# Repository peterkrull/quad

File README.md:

> [!TIP]
> The Rust-based flight control firmware is maintained in its own repository - [**Holsatus Flight**](https://github.com/holsatus/holsatus-flight)

---

# Project quad

This git repository is a personal project of mine to develop an open-source autonomous quad copter using cheap off-the-shelf components in conjunction with control theory and state estimation. As much as possible, any auxiliary tools and documentation I produce, will also be a part of the repository.

## Getting Rusty

The [firmware](/software/rusty-quad) is written in the Rust programming language. This is in contrast to most flight controllers (and embedded devices in general) which use C or C++. The reason for choosing Rust is quite simple: it is a modern language. It can guarantee many things about the validity of memory at compile time, allows for writing high-level code, that runs at low-level speeds, and feels good to write; once you become friendly with the borrow checker.

### [*YouTube* : Demo of wireless data plotting and responsive controls](https://www.youtube.com/watch?v=jQ53PiUz8Us)

---

## Directory contents

- **[3dparts](/3dparts/)** - 3D models used in the project as STEP and .obj files.
- **[docs](/docs/)** - Documentation and learning material used in the project.
- **[hardware](/hardware/)** - Schematics, and PCB layouts as well as finished gerber files.
- **[images](/images/)** - Photos used in readme and some documentation.
- **[software](/software/)** - Software related to the project, including simulations, firmware, etc.
- **[tests](/tests/)** - Results from test conducted during this project

---

## Related repositories

During this project, some additional tools were developed, that reside in their own repositories.

### Rust crates

- [Async no-std ICM-20948 driver](https://github.com/peterkrull/icm20948-async)
- [Dshot driver for RP2040 PIO](https://github.com/peterkrull/dshot-pio)
- [Magnetometer calibration algorithm](https://github.com/peterkrull/mag-calibrator-rs)
- [Linear multi-sensor Kalman filter](https://github.com/peterkrull/kalman_filter_rust/)
- [(Forked) no-std SBUS-parser](https://github.com/peterkrull/sbus)

---

## License

This work is licensed under GPLv3.

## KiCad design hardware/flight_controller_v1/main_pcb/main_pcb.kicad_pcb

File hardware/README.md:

# Hardware

While a perfboard-based flight controller is fully capable, it is also heavy, large and labor intensive to manufacture. A compact and integrated PCB is a natural next step to reduce complexity, increase flexibility and reproducability.

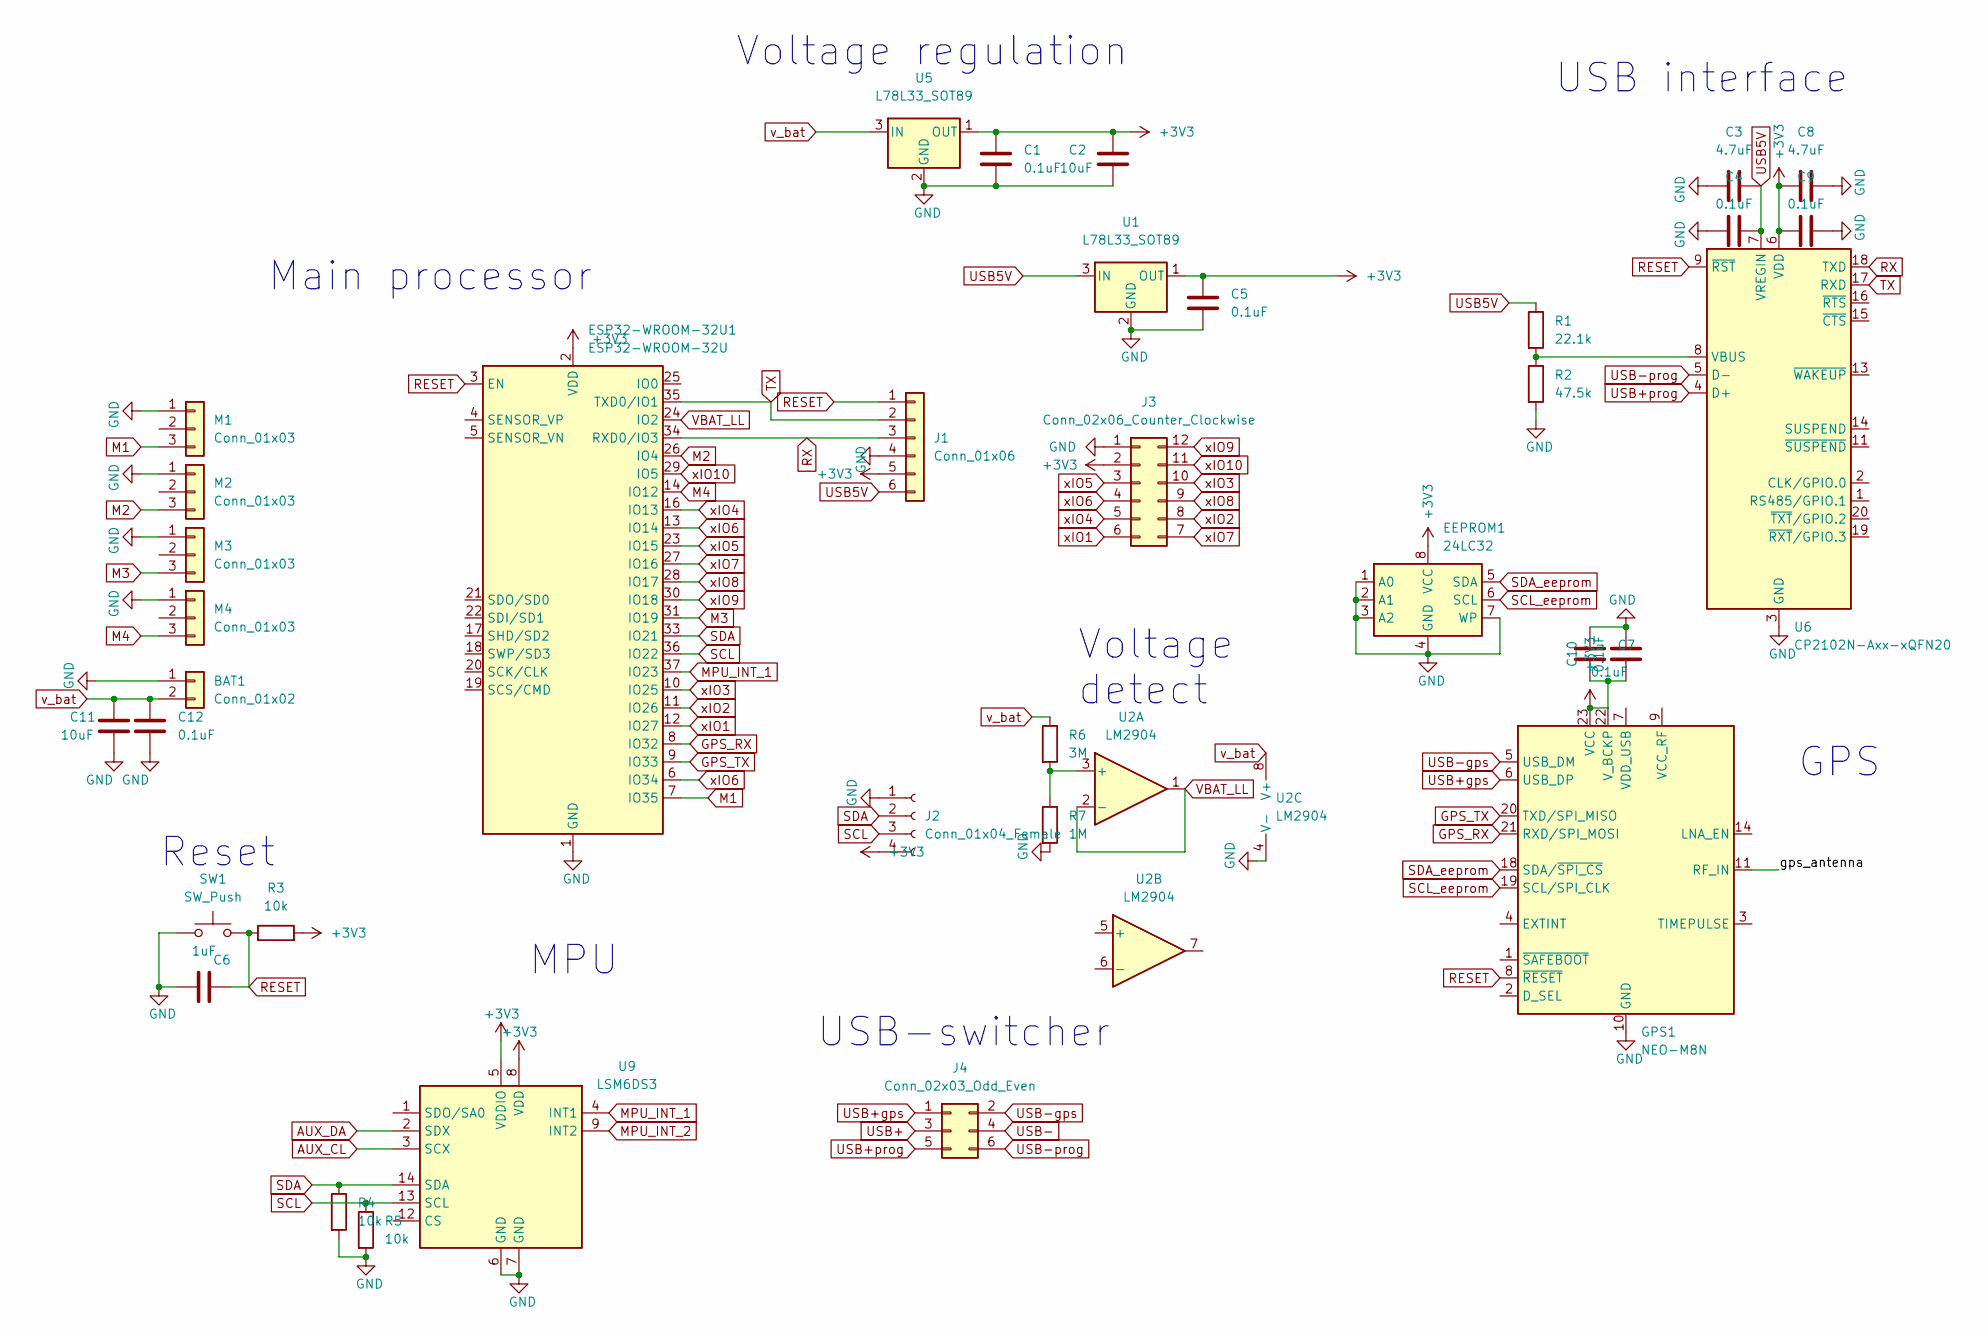
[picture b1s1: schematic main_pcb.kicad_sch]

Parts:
BAT1: Conn_01x02; PinHeader_1x02_P2.54mm_Vertical
C1, C4, C5, C7, C9, C10, C12: 0.1uF; C_0805_2012Metric
C2: 10uF; CP_Elec_5x4.5
C3, C8: 4.7uF; C_0805_2012Metric
C6: 1uF; C_0805_2012Metric
C11: 10uF; C_0805_2012Metric
EEPROM1: 24LC32; TSSOP-8_4.4x3mm_P0.65mm
ESP32-WROOM-32U1: ESP32-WROOM-32U
GPS1: NEO-M8N; ublox_NEO
J1: Conn_01x06; PinHeader_1x06_P2.54mm_Vertical
J2: Conn_01x04_Female; PinHeader_1x04_P2.54mm_Vertical
J3: Conn_02x06_Counter_Clockwise; PinHeader_2x06_P2.54mm_Vertical
J4: Conn_02x03_Odd_Even; PinHeader_2x03_P2.54mm_Vertical
M1, M2, M3, M4: Conn_01x03; PinHeader_1x03_P2.54mm_Vertical
R1: 22.1k; R_0805_2012Metric
R2: 47.5k; R_0805_2012Metric
R3, R4, R5: 10k; R_0805_2012Metric
R6: 3M; R_0805_2012Metric
R7: 1M; R_0805_2012Metric
SW1: SW_Push; SW_SPST_B3U-1000P-B
U1, U5: L78L33_SOT89; SOT-89-3
U2: LM2904; Diodes_PSOP-8
U6: CP2102N-Axx-xQFN20; MLF-20-1EP_4x4mm_P0.5mm_EP2.6x2.6mm
U9: LSM6DS3; LGA-14_3x2.5mm_P0.5mm_LayoutBorder3x4y

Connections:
+3V3: C1.1, C2.1, C5.1, C7.2, C8.1, C9.1, C10.1, EEPROM1.8 (VCC), ESP32-WROOM-32U1.2 (VDD), GPS1.22 (V_BCKP), GPS1.23 (VCC), J1.5, J2.4, J3.2, R3.2, U1.1 (OUT), U5.1 (OUT), U6.6 (VDD), U9.5 (VDDIO), U9.8 (VDD)
/gps_antenna: GPS1.11 (RF_IN); also elsewhere on the board
AUX_CL: U9.3 (SCX)
AUX_DA: U9.2 (SDX)
GND: BAT1.1, C1.2, C2.2, C3.1, C4.1, C5.2, C6.1, C7.1, C8.2, C9.2, C10.2, C11.2, C12.2, EEPROM1.1 (A0), EEPROM1.2 (A1), EEPROM1.3 (A2), EEPROM1.4 (GND), EEPROM1.7 (WP), ESP32-WROOM-32U1.1 (GND), ESP32-WROOM-32U1.15 (GND), ESP32-WROOM-32U1.38 (GND), ESP32-WROOM-32U1.39 (GND), GPS1.10 (GND), GPS1.12 (GND), GPS1.13 (GND), GPS1.24 (GND), J1.4, J2.1, J3.1, M1.1, M2.1, M3.1, M4.1, R2.2, R4.2, R5.2, R7.2, SW1.1, U1.2 (GND), U2.4 (V-), U5.2 (GND), U6.3 (GND), U6.12 (GND), U6.21 (GND), U9.6 (GND), U9.7 (GND); also elsewhere on the board
GPS_RX: ESP32-WROOM-32U1.8 (IO32), GPS1.21 (RXD/SPI_MOSI)
GPS_TX: ESP32-WROOM-32U1.9 (IO33), GPS1.20 (TXD/SPI_MISO)
M1: ESP32-WROOM-32U1.7 (IO35), M1.3
M2: ESP32-WROOM-32U1.26 (IO4), M2.3
M3: ESP32-WROOM-32U1.31 (IO19), M3.3
M4: ESP32-WROOM-32U1.14 (IO12), M4.3
MPU_INT_1: ESP32-WROOM-32U1.37 (IO23), U9.4 (INT1)
MPU_INT_2: U9.9 (INT2)
unnamed: R1.2, R2.1, U6.8 (VBUS)
unnamed: R6.2, R7.1, U2.3 (+)
RESET: C6.2, ESP32-WROOM-32U1.3 (EN), GPS1.8 (~RESET), J1.1, R3.1, SW1.2, U6.9 (~RST)
RX: ESP32-WROOM-32U1.34 (RXD0/IO3), J1.3, U6.18 (TXD)
SCL: ESP32-WROOM-32U1.36 (IO22), J2.3, R5.1, U9.13 (SCL)
SCL_eeprom: EEPROM1.6 (SCL), GPS1.19 (SCL/SPI_CLK)
SDA: ESP32-WROOM-32U1.33 (IO21), J2.2, R4.1, U9.14 (SDA)
SDA_eeprom: EEPROM1.5 (SDA), GPS1.18 (SDA/~SPI_CS)
TX: ESP32-WROOM-32U1.35 (TXD0/IO1), J1.2, U6.17 (RXD)
USB5V: C3.2, C4.2, J1.6, R1.1, U1.3 (IN), U6.7 (VREGIN); also elsewhere on the board
USB+: J4.3; also elsewhere on the board
USB+gps: GPS1.6 (USB_DP), J4.1
USB+prog: J4.5, U6.4 (D+)
USB-: J4.4; also elsewhere on the board
USB-gps: GPS1.5 (USB_DM), J4.2
USB-prog: J4.6, U6.5 (D-)
VBAT_LL: ESP32-WROOM-32U1.24 (IO2), U2.1, U2.2 (-)
v_bat: BAT1.2, C11.1, C12.1, R6.1, U2.8 (V+), U5.3 (IN)
xIO1: ESP32-WROOM-32U1.12 (IO27), J3.6
xIO2: ESP32-WROOM-32U1.11 (IO26), J3.8
xIO3: ESP32-WROOM-32U1.10 (IO25), J3.10
xIO4: ESP32-WROOM-32U1.16 (IO13), J3.5
xIO5: ESP32-WROOM-32U1.23 (IO15), J3.3
xIO6: ESP32-WROOM-32U1.6 (IO34), ESP32-WROOM-32U1.13 (IO14), J3.4
xIO7: ESP32-WROOM-32U1.27 (IO16), J3.7
xIO8: ESP32-WROOM-32U1.28 (IO17), J3.9
xIO9: ESP32-WROOM-32U1.30 (IO18), J3.12
xIO10: ESP32-WROOM-32U1.29 (IO5), J3.11

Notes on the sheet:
Voltage detect
USB-switcher
Reset
GPS
MPU
Main processor
Voltage regulation
USB interface

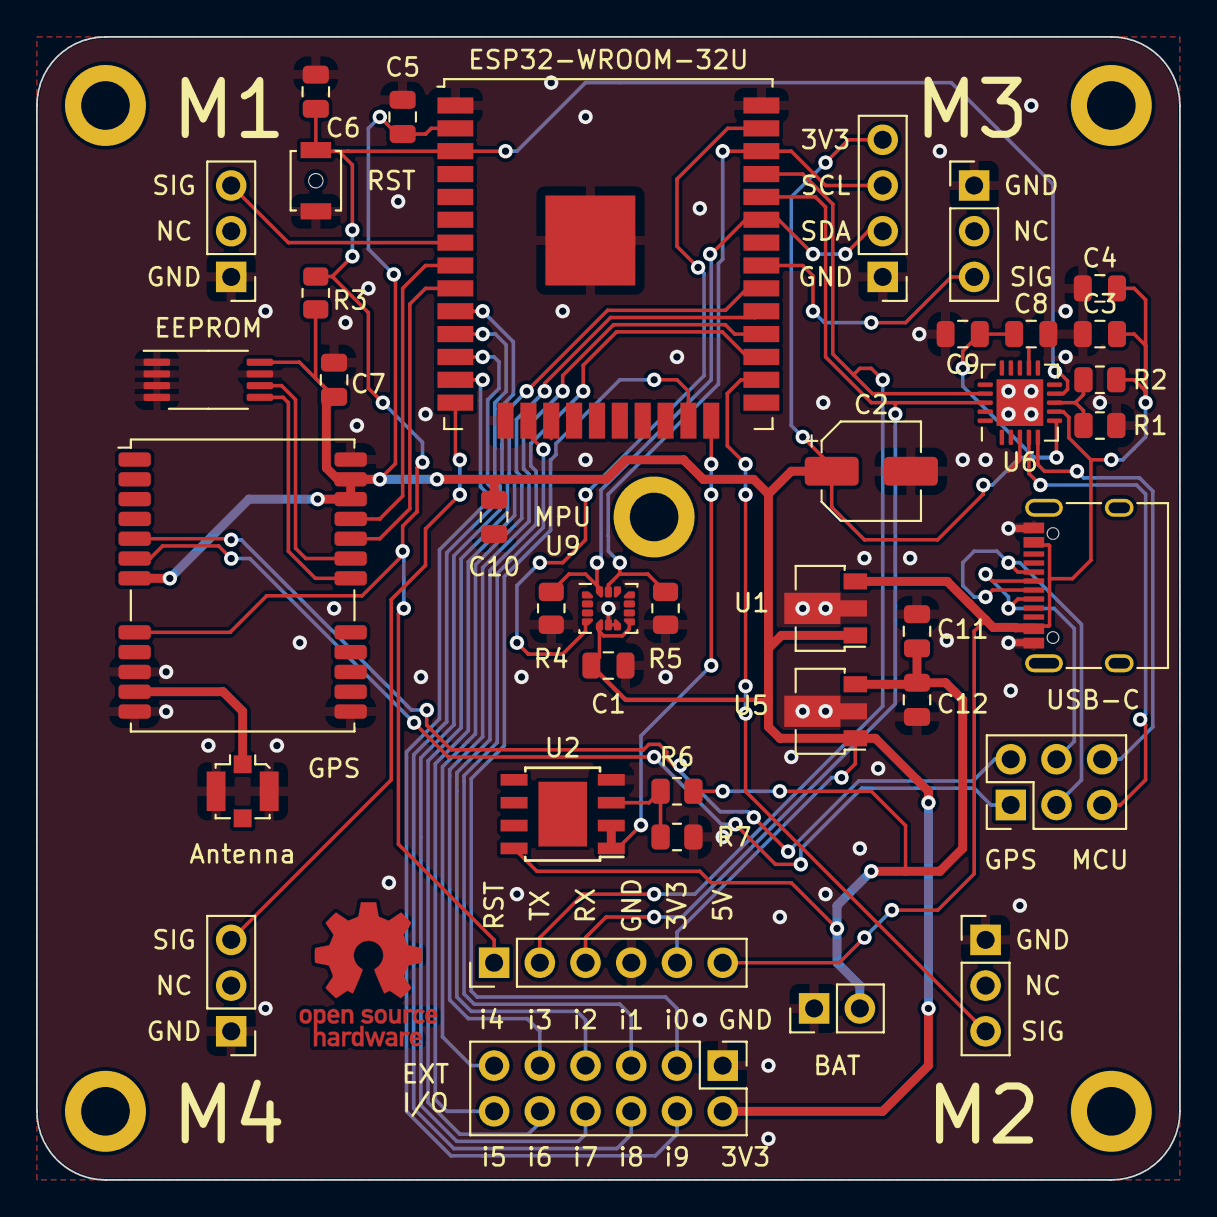
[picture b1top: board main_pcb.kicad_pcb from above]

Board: 2 copper layers, 63.5 x 63.5 mm, 39 parts (0 on the bottom side), 38 nets.

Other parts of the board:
Antenna: U.FL; U.FL_Molex_MCRF_73412-0110_Vertical
USB-C: USB_C_Receptacle_XKB_U262-16XN-4BVC11

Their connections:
/gps_antenna: Antenna.1; also elsewhere on the board
GND: Antenna.2, USB-C.A1, USB-C.A12, USB-C.B1, USB-C.B12; also elsewhere on the board
USB5V: USB-C.A4, USB-C.A9, USB-C.B4, USB-C.B9; also elsewhere on the board
USB+: USB-C.A6, USB-C.B6; also elsewhere on the board
USB-: USB-C.A7, USB-C.B7; also elsewhere on the board

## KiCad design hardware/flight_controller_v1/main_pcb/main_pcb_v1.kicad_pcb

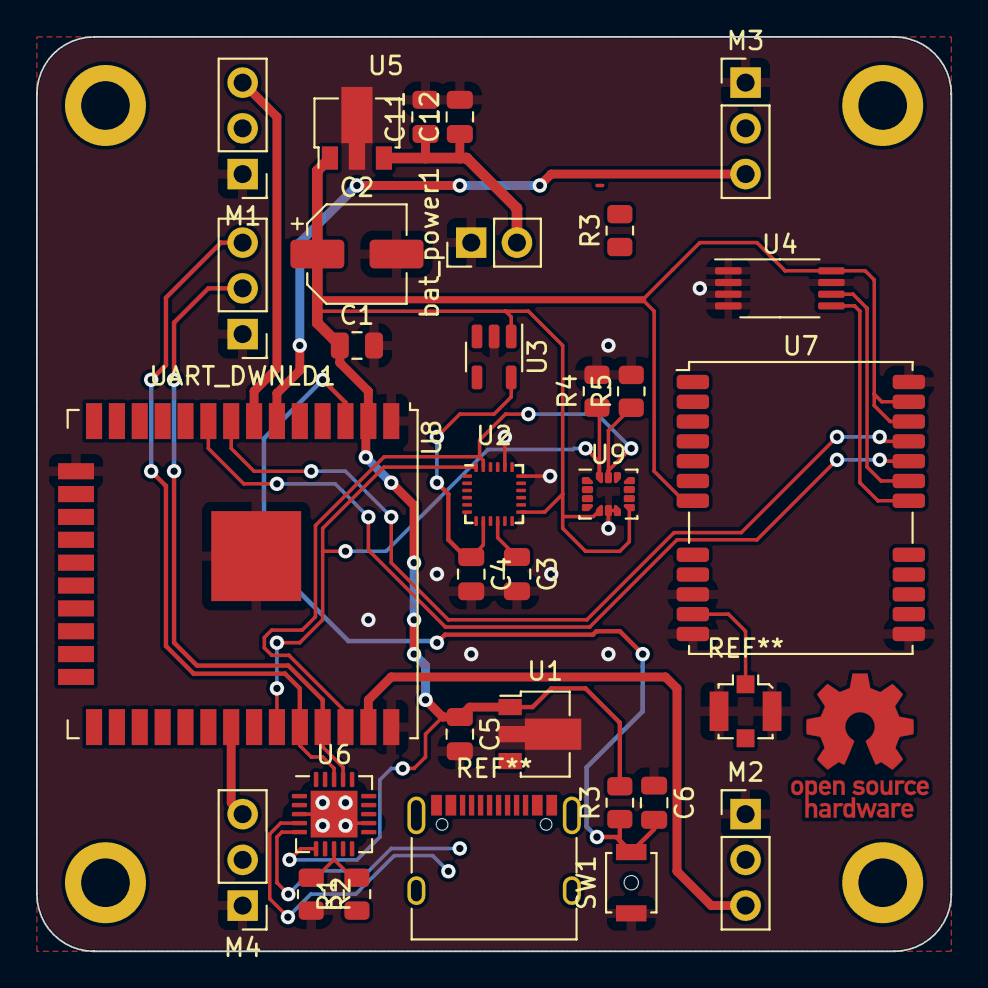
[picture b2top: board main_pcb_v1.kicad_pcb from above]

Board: 2 copper layers, 50.8 x 50.8 mm, 30 parts (0 on the bottom side), 19 nets.

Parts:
C1, C3, C4, C5, C12: 0.1uF; C_0805_2012Metric
C2: 10uF; CP_Elec_5x4.5
C6: 1uF; C_0805_2012Metric
C11: 10uF; C_0805_2012Metric
M1, M2, M3, M4: Conn_01x03; PinHeader_1x03_P2.54mm_Vertical
R1: 22.1k; R_0805_2012Metric
R2: 47.5k; R_0805_2012Metric
R3, R4, R5: 10k; R_0805_2012Metric
R3#2: R; R_0805_2012Metric
SW1: SW_Push; SW_SPST_B3U-1000P-B
U1, U5: L78L33_SOT89; SOT-89-3
U2: ICM-20948; InvenSense_QFN-24_3x3mm_P0.4mm
U3: TLV70018_SOT23-5; SOT-23-5
U4: 24LC32; TSSOP-8_4.4x3mm_P0.65mm
U6: CP2102N-Axx-xQFN20; MLF-20-1EP_4x4mm_P0.5mm_EP2.6x2.6mm
U7: NEO-M8N; ublox_NEO
U8: ESP32-WROOM-32U
U9: LSM6DS3; LGA-14_3x2.5mm_P0.5mm_LayoutBorder3x4y
UART_DWNLD1: Conn_01x03; PinHeader_1x03_P2.54mm_Vertical
bat_power1: Conn_01x02; PinHeader_1x02_P2.54mm_Vertical

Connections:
+1V8: C4.1, U2.8 (VDDIO), U3.5 (OUT)
+3V3: C1.1, C2.1, C5.1, R3.2, U1.1 (OUT), U2.13 (VDD), U3.1 (IN), U4.8 (VCC), U5.1 (OUT), U6.6 (VDD), U7.7 (VDD_USB), U7.22 (V_BCKP), U7.23 (VCC), U8.2 (VDD), U9.5 (VDDIO), U9.8 (VDD)
GND: C1.2, C2.2, C3.2, C4.2, C5.2, C6.1, C11.2, C12.2, M1.1, M2.1, M3.1, M4.1, R2.2, R4.2, R5.2, SW1.1, U1.2 (GND), U2.18 (GND), U2.20 (GND), U3.2 (GND), U4.1 (A0), U4.2 (A1), U4.3 (A2), U4.4 (GND), U4.7 (WP), U5.2 (GND), U6.3 (GND), U6.12 (GND), U6.21 (GND), U7.10 (GND), U7.12 (GND), U7.13 (GND), U7.24 (GND), U8.1 (GND), U8.15 (GND), U8.38 (GND), U8.39 (GND), U9.6 (GND), U9.7 (GND), UART_DWNLD1.1, bat_power1.1
GPS_RX: U7.21 (RXD/SPI_MOSI), U8.8 (IO32)
GPS_TX: U7.20 (TXD/SPI_MISO), U8.9 (IO33)
M1: M1.3, U8.7 (IO35)
M2: M2.3, U8.37 (IO23)
M3: M3.3, U8.6 (IO34)
M4: M4.3, U8.31 (IO19)
unnamed: C3.1, U2.10 (REGOUT)
unnamed: R1.2, R2.1, U6.8 (VBUS)
RESET: C6.2, R3.1, SW1.2, U8.3 (EN)
RX: U6.18 (TXD), U8.34 (RXD0/IO3), UART_DWNLD1.3
SCL: R5.1, U2.23 (SCL/SCLK), U8.36 (IO22), U9.13 (SCL)
SCL_eeprom: U4.6 (SCL), U7.19 (SCL/SPI_CLK)
SDA: R4.1, U2.24 (SDA/SDI), U8.33 (IO21), U9.14 (SDA)
SDA_eeprom: U4.5 (SDA), U7.18 (SDA/~SPI_CS)
TX: U6.17 (RXD), U8.35 (TXD0/IO1), UART_DWNLD1.2
v_bat: C11.1, C12.1, U5.3 (IN), bat_power1.2

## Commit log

2021-12-21 Initial folder structure and TOC for readme added
2021-12-21 Fixed typo in readme causing image not to display
2021-12-21 Added initial firmware and 3D models
2021-12-21 Moved libraries to lib folder
2021-12-21 Added wifi credentials to gitignore
2021-12-21 Added several object and functions to main firmware
2021-12-21 Added image to 3dparts folder
2021-12-21 Simplified line in readme
2021-12-21 Updated readme with disclaimer and project goals
2021-12-21 Fixed check list in readme
2021-12-21 Added sigProc library with PID controller
2022-01-25 Updated ESP32 software to support flight and ground programs, added initial python ground software
2022-02-14 Feb update
2022-02-14 Added 3D model for thrust test stand
2022-02-15 Tested and documented determination of thrust time constant
2022-02-15 Added documentation markdown for previous commit
2022-02-15 Added tools for thrust step documentation
2022-02-15 Small changes to thrust test doc
2022-02-18 Updated motor governing code, added few 3D models
2022-02-18 Corrected few spelling errors in doc
2022-02-24 Updated main
2022-02-24 Added matlab files
2022-02-27 Additional tests and documentation added for motor model and roll/pitch equations of motion
2022-02-27 Updated main flight program
2022-03-01 Added 32 cm spacers for wider drone test stand
2022-03-12 Added extra 3D parts for 32 cm test stand
2022-03-12 Updated readme and modelling of drone doc
2022-03-13 Added test and documentation for roll moment of inertia
2022-03-13 Added optional output limiter to PID controller
2022-03-13 Added anti-windup to PID integrator
2022-03-13 Updated roll simulink file
2022-03-13 Updated few docs
2022-03-17 First attempt at ipynb Octave document
2022-04-21 Added initial kicad main-pcb
2022-04-21 Slight changes to PCB
2022-04-24 Major changes to main code structure. More modularity incoming
2022-04-24 New PCB iteration
2022-04-24 Removed sensitive information
2022-04-24 Updated a few simulation files
2022-04-24 Added default wifi_credentials file
2022-04-24 Tweaks to readmes
2022-04-24 Workspace
2022-04-24 Non-important
2022-04-24 Small metatext to 3dparts readme
2022-04-24 Added gerber files for current version of PCB
2022-04-24 Added some photos to hardware readme
2022-04-30 Code restructure
2022-05-08 Update main flight code
2022-05-08 Added firmware for gathering data
2022-05-08 Added test data for kalman filter test
2022-08-08 Code restructuring in progress..
2022-08-09 Updated readmes, removed old files and updates some folder structures
2022-08-20 Added Functional Kalman filter implementation in Python
2022-08-20 Added test file for Python KF
2022-08-27 Update kalman filtering python code
2022-08-27 Added readmes and project goal tracker
2022-08-28 Added Quaternion and controllers python files
2022-12-07 Mega update to fligth firmware
2022-12-07 Slight modifications to local libraries
2022-12-09 Updated readme to include video
2022-12-10 Updated picture in readme
2022-12-10 Added image
2022-12-10 Compressed readme image
2022-12-12 Added UDP plotter
2022-12-12 Added julia data structures
2023-02-23 Added readme to software section
2023-03-15 Added initial Rusty flight controller
2023-03-15 Removed unreleased module from imports
2023-03-15 Deleted unused python files
2023-03-16 Cleanup of various old files
2023-03-29 Added settings.json with specific cargo target
2023-03-29 Match different switch C positions to throttle profile
2023-04-11 Fixed issue causing yaw wrapping to not work as intended
2023-04-13 Add stl for legs and battery holder
2023-04-22 Made some functions generic for all floats
2023-04-22 Many changes to controller structure for much faster controls
2023-04-22 Updated toml
2023-04-23 Removed outdated notebook
2023-04-23 Removed unused Python files
2023-04-23 Moved from Matlab to Julia for processing of test data (inertia)
2023-04-23 Updated inertia measurement doc
2023-04-23 Converted another doc to Julia
2023-04-24 Changed last matlab file to julia
2023-04-25 Added entry to .vscode/settings.json to fix rust-analyzer macro bug
2023-04-25 Restructure. All tasks are moved to seperate modules. Added shared i2c-bus support.
2023-04-25 Moved hard-coded motor directions into main file
2023-05-06 Create LICENSE
2023-05-06 Added small license blurb to README
2023-07-02 Added magnetometer feature flag to flight controller. Uses updated quad-dshot-pio crate
2023-07-06 WIP starting framework for shared IMU traits
2023-09-09 Overhaul to message passing in software architechture
2023-09-09 Added document describing idea behind current firmware architechture
2023-09-09 Updated url in readme
2023-09-09 Added rusty_quad_diagram.drawio source file
2024-03-13 Added Holsatus Flight as submodule
2026-03-17 Add tip about Holsatus Flight to README
